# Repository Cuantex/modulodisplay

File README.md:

# modulodisplay
# modulodisplay

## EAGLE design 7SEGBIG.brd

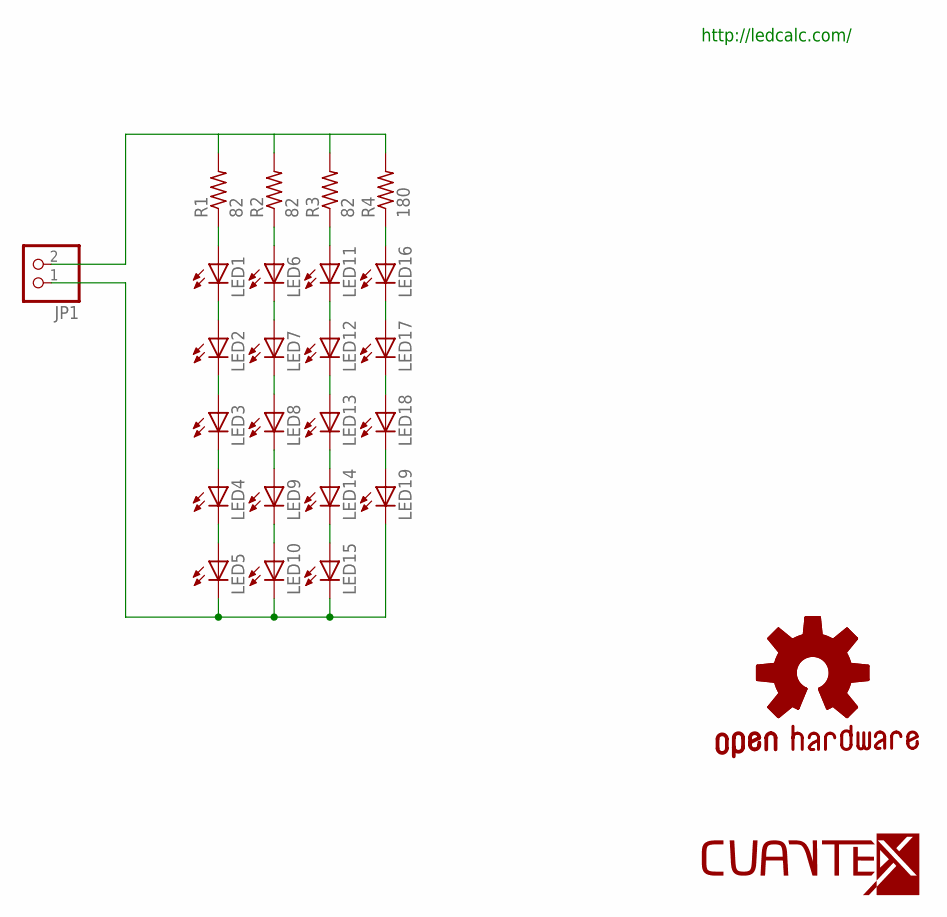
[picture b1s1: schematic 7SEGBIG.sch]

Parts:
GOLD_ORB_SM1: OSHWLOGO_GOLD_ORB_LG; OSHW0
JP1: PINHD-1X2/90; 1X02/90
LED1, LED2, LED3, LED4, LED5, LED6, LED7, LED8, LED9, LED10, LED11, LED12, LED13, LED14, LED15, LED16, LED17, LED18, LED19: LEDKA-3528ASYC; KA-3528ASYC
R1, R2, R3: 82; R1206
R4: 180; R1206
U$3: LOGO-TOP-10MM; C-000

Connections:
GND: JP1.1, LED5.C, LED10.C, LED15.C, LED19.C
unnamed: LED1.A, R1.1
unnamed: LED6.A, R2.1
unnamed: LED11.A, R3.1
unnamed: LED16.A, R4.1
unnamed: LED16.C, LED17.A
unnamed: LED11.C, LED12.A
unnamed: LED6.C, LED7.A
unnamed: LED1.C, LED2.A
unnamed: LED2.C, LED3.A
unnamed: LED7.C, LED8.A
unnamed: LED12.C, LED13.A
unnamed: LED17.C, LED18.A
unnamed: LED18.C, LED19.A
unnamed: LED13.C, LED14.A
unnamed: LED8.C, LED9.A
unnamed: LED3.C, LED4.A
unnamed: LED14.C, LED15.A
unnamed: LED9.C, LED10.A
unnamed: LED4.C, LED5.A
unnamed: JP1.2, R1.2, R2.2, R3.2, R4.2

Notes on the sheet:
http://ledcalc.com/

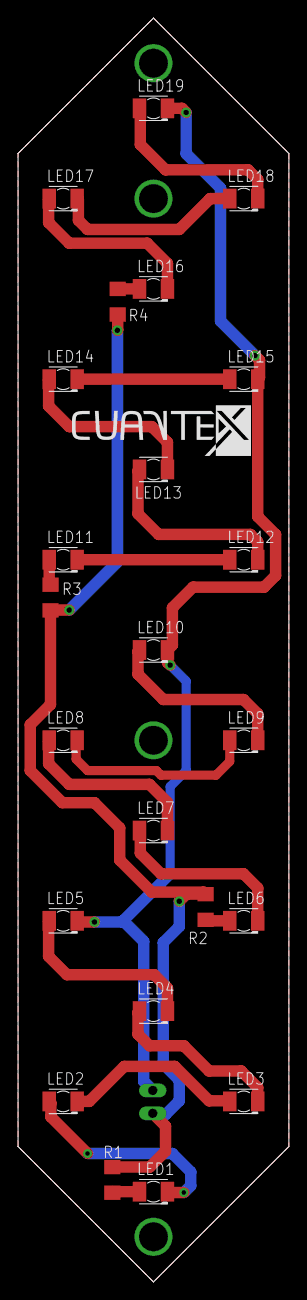
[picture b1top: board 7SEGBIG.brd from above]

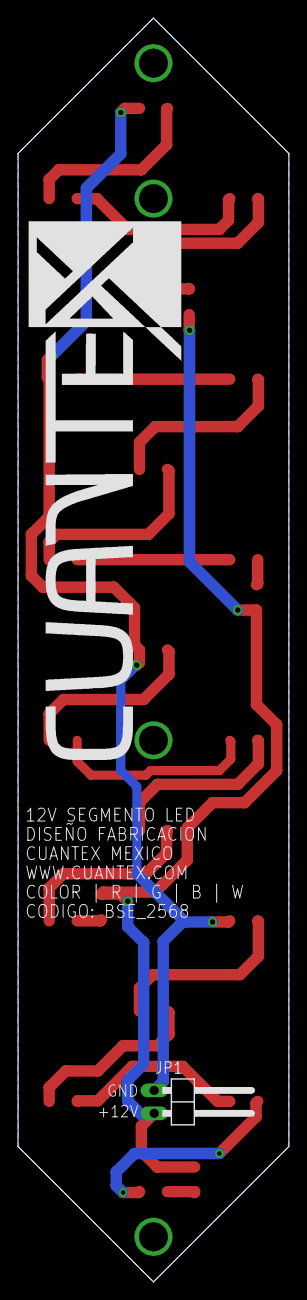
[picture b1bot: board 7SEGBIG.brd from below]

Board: 2 copper layers, 30.0 x 140.0 mm, 28 parts (2 on the bottom side), 21 nets.

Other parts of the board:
U$1: C-0
U$2: C-4

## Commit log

2016-09-03 Archivos en git
